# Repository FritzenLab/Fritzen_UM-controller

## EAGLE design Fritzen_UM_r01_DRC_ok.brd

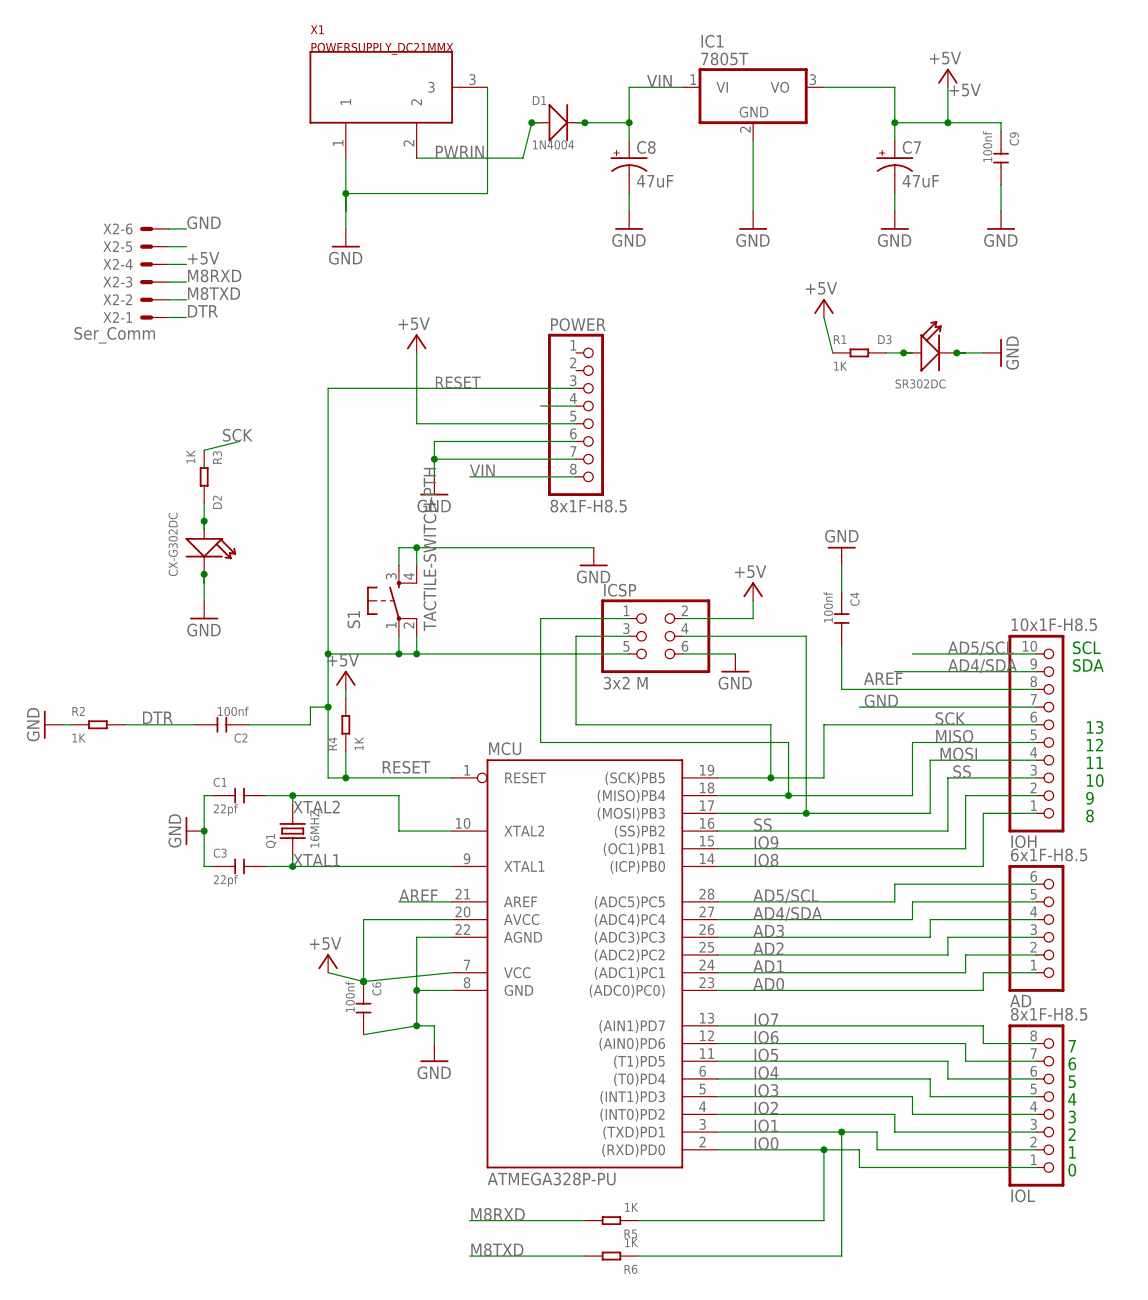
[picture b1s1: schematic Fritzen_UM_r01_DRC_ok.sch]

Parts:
AD: 6x1F-H8.5; 1X06
C1, C3: 22pf; CERAMIC-2.54
C2, C4, C6, C9: 100nf; CERAMIC-2.54
C7, C8: 47uF; E3,5-8
D1: 1N4004; DO-41
D2: CX-G302DC; LED2-2.54-D3.0MM
D3: SR302DC; LED2-2.54-D3.0MM
IC1: 7805T; TO220H
ICSP: 3x2 M; 2X03
IOH: 10x1F-H8.5; 1X10
IOL: 8x1F-H8.5; 1X08
MCU: ATMEGA328P-PU; DIL28-3
POWER: 8x1F-H8.5; 1X08
Q1: 16MHZ; HC49US
R1, R2, R3, R4, R5, R6: 1K; PR-D2.3XL6.5MM
S1: TACTILE-SWITCH-PTH; TAC-SWITCH-PTH
X1: POWERSUPPLY_DC21MMX; POWERSUPPLY_DC-21MM
X2: Ser_Comm; 22-23-2061

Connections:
+5V: C6.1, C7.+, C9.1, IC1.3 (VO), ICSP.2, MCU.7 (VCC), MCU.20 (AVCC), POWER.5, R1.1, R4.2, X2.4
AD0: AD.1, MCU.23 ((ADC0)PC0))
AD1: AD.2, MCU.24 ((ADC1)PC1)
AD2: AD.3, MCU.25 ((ADC2)PC2)
AD3: AD.4, MCU.26 ((ADC3)PC3)
AD4/SDA: AD.5, IOH.9, MCU.27 ((ADC4)PC4)
AD5/SCL: AD.6, IOH.10, MCU.28 ((ADC5)PC5)
AREF: C4.2, IOH.8, MCU.21 (AREF)
DTR: C2.2, R2.2, X2.1
GND: C1.1, C3.1, C4.1, C6.2, C7.-, C8.-, C9.2, D2.K (-), D3.K (-), IC1.2 (GND), ICSP.6, IOH.7, MCU.8 (GND), MCU.22 (AGND), POWER.6, POWER.7, R2.1, S1.3, S1.4, X1.1, X1.3, X2.6
IO0: IOL.1, MCU.2 ((RXD)PD0), R5.1
IO1: IOL.2, MCU.3 ((TXD)PD1), R6.1
IO2: IOL.3, MCU.4 ((INT0)PD2)
IO3: IOL.4, MCU.5 ((INT1)PD3)
IO4: IOL.5, MCU.6 ((T0)PD4)
IO5: IOL.6, MCU.11 ((T1)PD5)
IO6: IOL.7, MCU.12 ((AIN0)PD6)
IO7: IOL.8, MCU.13 ((AIN1)PD7)
IO8: IOH.1, MCU.14 ((ICP)PB0)
IO9: IOH.2, MCU.15 ((OC1)PB1)
M8RXD: R5.2, X2.3
M8TXD: R6.2, X2.2
MISO: ICSP.1, IOH.5, MCU.18 ((MISO)PB4)
MOSI: ICSP.4, IOH.4, MCU.17 ((MOSI)PB3)
unnamed: D2.A (+), R3.2
unnamed: D3.A (+), R1.2
PWRIN: D1.1 (+), X1.2
RESET: C2.1, ICSP.5, MCU.1 (RESET), POWER.3, R4.1, S1.1, S1.2
SCK: ICSP.3, IOH.6, MCU.19 ((SCK)PB5), R3.1
SS: IOH.3, MCU.16 ((SS)PB2)
VIN: C8.+, D1.2 (-), IC1.1 (VI), POWER.8
XTAL1: C3.2, MCU.9 (XTAL1), Q1.1
XTAL2: C1.2, MCU.10 (XTAL2), Q1.2

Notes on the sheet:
SDA
SCL

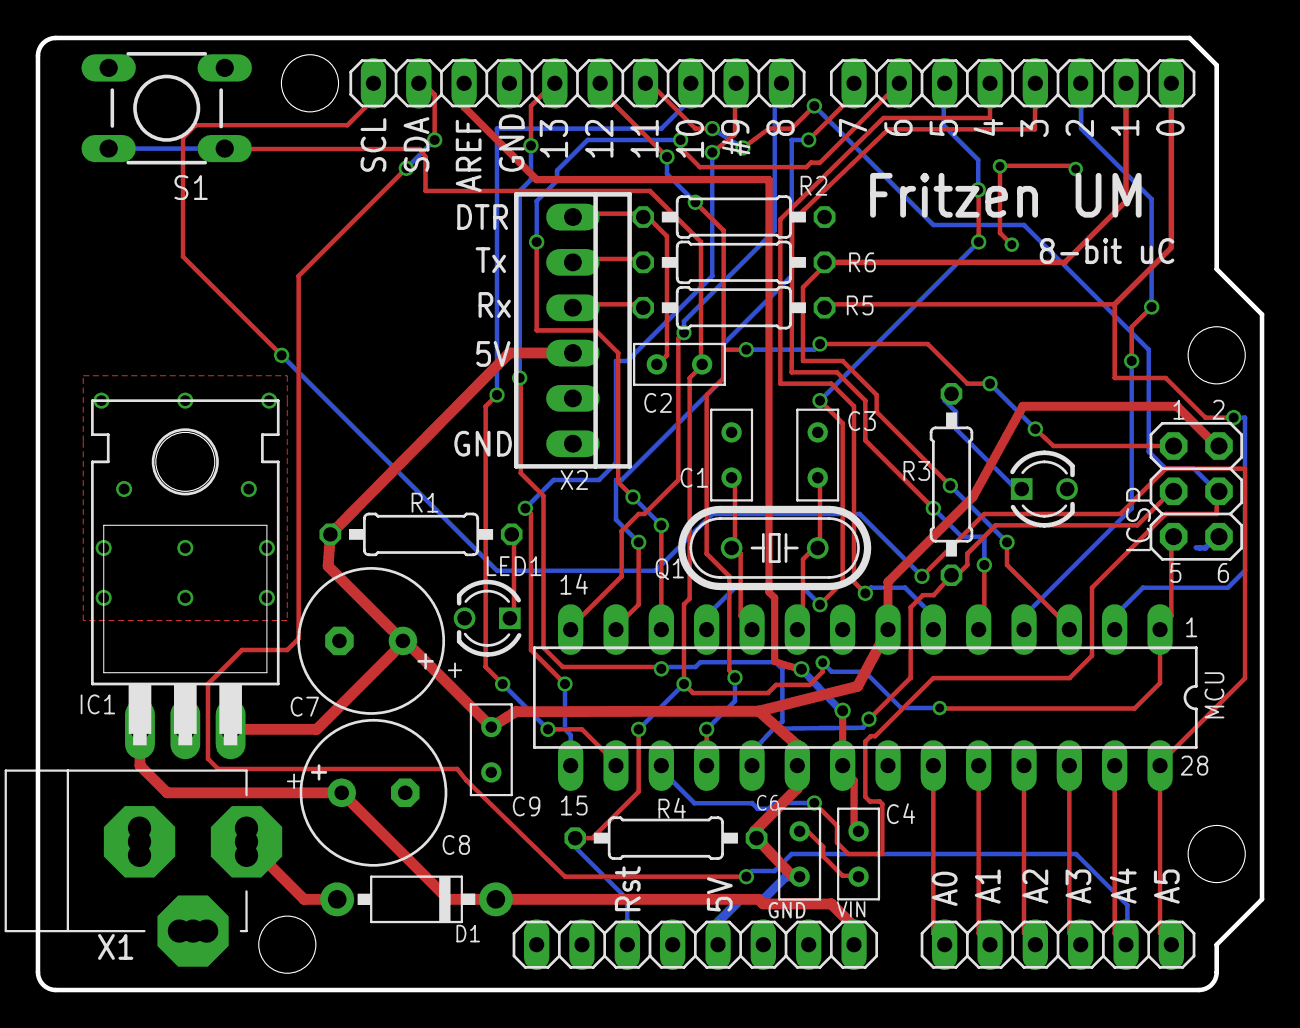
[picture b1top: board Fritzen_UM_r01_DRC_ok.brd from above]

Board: 2 copper layers, 68.6 x 53.3 mm, 28 parts (0 on the bottom side), 33 nets.

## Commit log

2016-02-04 Primeiro commit da placa Fritzen_UM
    Primeiro commit da placa Fritzen_UM, compatível com o Arduino UNO
2016-02-04 adicionado diagrama esquemático
    havia esquecido dele no primeiro commit
2016-02-25 Second release of the PCB and schematic
    Corrections made to the PCB silkcreen and traces (due to clearances and
    other issues). Please do not produce any version older than this one.
2016-03-23 Cleaning PCB and Fabrication files
    I have order 30 pieces of this board revision at MakerStudio.cc

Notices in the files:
parts and their libraries:
GeekAmmo: Licensing:Creative Commons ShareAlike 4.0 International - https://creativecommons.org/licenses/by-sa/4.0
